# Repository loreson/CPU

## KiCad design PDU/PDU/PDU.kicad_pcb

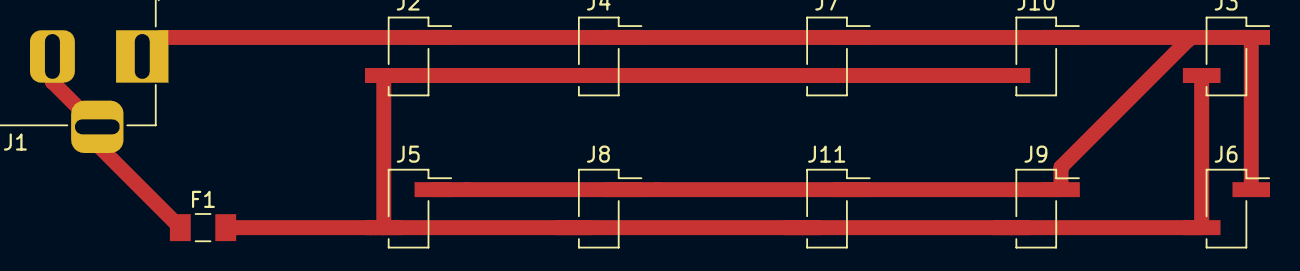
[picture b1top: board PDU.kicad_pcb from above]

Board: 2 copper layers, 12 parts (0 on the bottom side), 3 nets.

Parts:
F1: Fuse_Small; Fuse_1206_3216Metric_Pad1.39x1.80mm_HandSolder
J1: Barrel_Jack; BarrelJack_Horizontal
J2, J3, J4, J5, J6, J7, J8, J9, J10, J11: Conn_01x02_Male; PinHeader_1x02_P2.54mm_Vertical_SMD_Pin1Right

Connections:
unnamed: F1.1, J1.2, J1.3
unnamed: F1.2, J2.2, J3.2, J4.2, J5.2, J6.2, J7.2, J8.2, J9.2, J10.2, J11.2
unnamed: J1.1, J2.1, J3.1, J4.1, J5.1, J6.1, J7.1, J8.1, J9.1, J10.1, J11.1

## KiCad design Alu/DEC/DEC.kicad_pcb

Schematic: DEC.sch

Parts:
C1, C2: 100nF; C_0805_2012Metric_Pad1.29x1.40mm_HandSolder
J1: Conn_01x08; PinHeader_1x08_P2.54mm_Vertical
J2: Conn_01x09; PinHeader_1x09_P2.54mm_Vertical
J3: Conn_01x02; PinHeader_1x02_P2.54mm_Vertical
R10, R11, R12: 0; R_1206_3216Metric_Pad1.39x1.80mm_HandSolder
U1, U2: 74LS283; SOIC-16_3.9x9.9mm_P1.27mm

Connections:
/C_OUT: J2.1, U2.9; also elsewhere on the board
/X0: J1.8, U1.5
/X1: J1.7, U1.3
/X2: J1.6, U1.14
/X3: J1.5, U1.12
/X4: J1.4, U2.5
/X5: J1.3, U2.3
/X6: J1.2, U2.14
/X7: J1.1, U2.12
/Z0: J2.9, U1.4; also elsewhere on the board
/Z1: J2.8, U1.1; also elsewhere on the board
/Z2: J2.7, U1.13; also elsewhere on the board
/Z3: J2.6, R11.1; also elsewhere on the board
/Z4: J2.5, U2.4; also elsewhere on the board
/Z5: J2.4, U2.1; also elsewhere on the board
/Z6: J2.3, U2.13; also elsewhere on the board
/Z7: J2.2, R10.1; also elsewhere on the board
GND: C1.2, C2.2, J3.2, R12.1, R12.2, U1.7, U1.8, U2.8; also elsewhere on the board
unnamed: R10.2, U2.10
unnamed: R11.2, U1.10
unnamed: U1.9, U2.7
VCC: C1.1, C2.1, J3.1, U1.2, U1.6, U1.11, U1.15, U1.16, U2.2, U2.6, U2.11, U2.15, U2.16; also elsewhere on the board

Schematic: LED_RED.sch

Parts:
D1: RED; LED_0805_2012Metric_Pad1.12x1.40mm_HandSolder
Q1: 2N7002; SOT-23
R1: 1k; R_0805_2012Metric

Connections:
/Z0: Q1.1 (G); also elsewhere on the board
GND: Q1.2 (S); also elsewhere on the board
unnamed: D1.1, R1.1
unnamed: Q1.3 (D), R1.2
VCC: D1.2; also elsewhere on the board

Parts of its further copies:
D2, D3, D4, D5, D6, D7, D9: RED; LED_0805_2012Metric_Pad1.12x1.40mm_HandSolder
Q2, Q3, Q4, Q5, Q6, Q7, Q9: 2N7002; SOT-23
R2, R3, R4, R5, R6, R7, R9: 1k; R_0805_2012Metric

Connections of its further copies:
/Z1: Q2.1 (G); also elsewhere on the board
/Z2: Q3.1 (G); also elsewhere on the board
/Z3: Q4.1 (G); also elsewhere on the board
/Z4: Q5.1 (G); also elsewhere on the board
/Z5: Q6.1 (G); also elsewhere on the board
/Z6: Q7.1 (G); also elsewhere on the board
/Z7: Q9.1 (G); also elsewhere on the board
GND: Q2.2 (S), Q3.2 (S), Q4.2 (S), Q5.2 (S), Q6.2 (S), Q7.2 (S), Q9.2 (S); also elsewhere on the board
unnamed: D2.1, R2.1
unnamed: D3.1, R3.1
unnamed: D4.1, R4.1
unnamed: D5.1, R5.1
unnamed: D6.1, R6.1
unnamed: D7.1, R7.1
unnamed: D9.1, R9.1
unnamed: Q2.3 (D), R2.2
unnamed: Q3.3 (D), R3.2
unnamed: Q4.3 (D), R4.2
unnamed: Q5.3 (D), R5.2
unnamed: Q6.3 (D), R6.2
unnamed: Q7.3 (D), R7.2
unnamed: Q9.3 (D), R9.2
VCC: D2.2, D3.2, D4.2, D5.2, D6.2, D7.2, D9.2; also elsewhere on the board

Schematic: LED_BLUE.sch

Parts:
D8: BLUE; LED_0805_2012Metric_Pad1.12x1.40mm_HandSolder
Q8: 2N7002; SOT-23
R8: 820R; R_0805_2012Metric_Pad1.29x1.40mm_HandSolder

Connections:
/C_OUT: Q8.1 (G); also elsewhere on the board
GND: Q8.2 (S); also elsewhere on the board
unnamed: D8.1, R8.1
unnamed: Q8.3 (D), R8.2
VCC: D8.2; also elsewhere on the board

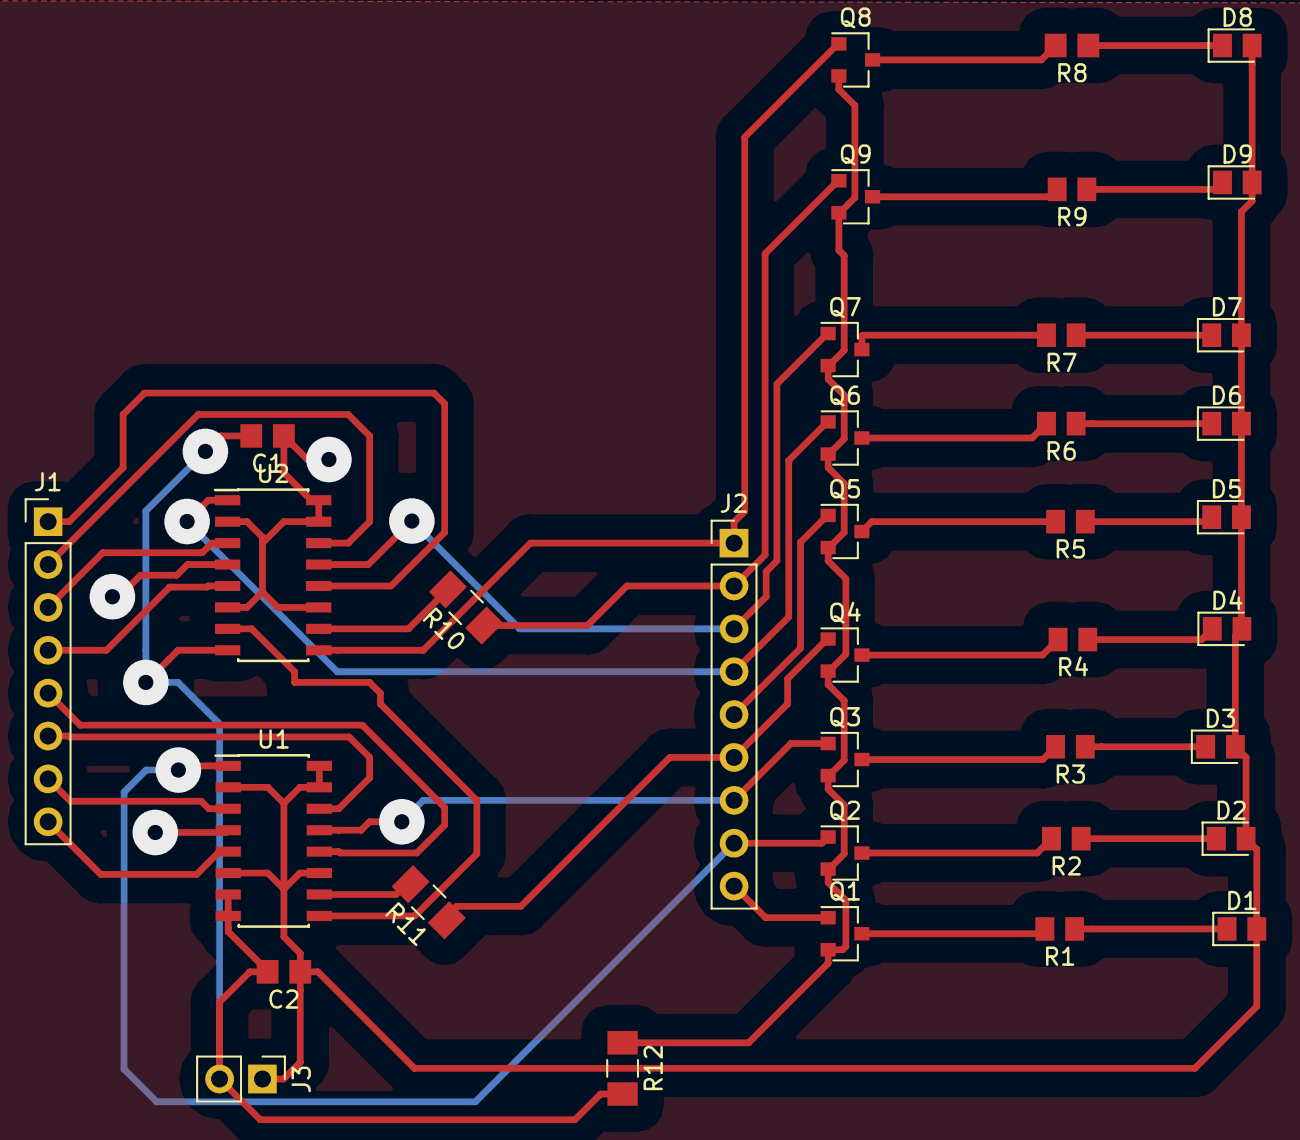
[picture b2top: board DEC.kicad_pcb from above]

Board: 4 copper layers, 37 parts (0 on the bottom side), 40 nets.

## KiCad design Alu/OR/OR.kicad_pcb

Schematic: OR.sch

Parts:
C1, C2: 100nF; C_0805_2012Metric
J1, J2, J4: Conn_01x08; PinHeader_1x08_P2.54mm_Vertical
J3: Conn_01x02_Male; PinHeader_1x02_P2.54mm_Vertical
R1, R2, R3: 0; R_1206_3216Metric_Pad1.39x1.80mm_HandSolder
U1, U2: 74LS32; SOIC-14_3.9x8.7mm_P1.27mm

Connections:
/X0: J1.8, U1.1
/X1: J1.7, U1.4
/X2: J1.6, U1.9
/X3: J1.5, U1.12
/X4: J1.4, U2.1
/X5: J1.3, U2.4
/X6: J1.2, U2.9
/X7: R2.1, U2.12
/Y0: J2.8, U1.2
/Y1: J2.7, U1.5
/Y2: J2.6, U1.10
/Y3: J2.5, U1.13
/Y4: R1.1, U2.2
/Y5: J2.3, U2.5
/Y6: J2.2, U2.10
/Y7: J2.1, U2.13
/Z0: J4.8, U1.3; also elsewhere on the board
/Z1: J4.7, U1.6; also elsewhere on the board
/Z2: J4.6, U1.8; also elsewhere on the board
/Z3: J4.5, U1.11; also elsewhere on the board
/Z4: J4.4, U2.3; also elsewhere on the board
/Z5: J4.3, U2.6; also elsewhere on the board
/Z6: J4.2, R3.1, U2.8
/Z7: J4.1, U2.11; also elsewhere on the board
/sheet5C411B65/X: R3.2; also elsewhere on the board
GND: C1.2, C2.2, J3.2, U1.7, U2.7; also elsewhere on the board
unnamed: J1.1, R2.2
unnamed: J2.4, R1.2
VCC: C1.1, C2.1, J3.1, U1.14, U2.14; also elsewhere on the board

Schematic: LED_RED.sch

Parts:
D1: RED; LED_0805_2012Metric_Pad1.12x1.40mm_HandSolder
Q1: 2N7002; SOT-23
R4: 1k; R_0805_2012Metric

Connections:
/Z0: Q1.1 (G); also elsewhere on the board
GND: Q1.2 (S); also elsewhere on the board
unnamed: D1.1, R4.1
unnamed: Q1.3 (D), R4.2
VCC: D1.2; also elsewhere on the board

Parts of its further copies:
D2, D3, D4, D5, D6, D7, D8: RED; LED_0805_2012Metric_Pad1.12x1.40mm_HandSolder
Q2, Q3, Q4, Q5, Q6, Q7, Q8: 2N7002; SOT-23
R5, R6, R7, R8, R9, R10, R11: 1k; R_0805_2012Metric

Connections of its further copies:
/Z1: Q2.1 (G); also elsewhere on the board
/Z2: Q3.1 (G); also elsewhere on the board
/Z3: Q4.1 (G); also elsewhere on the board
/Z4: Q5.1 (G); also elsewhere on the board
/Z5: Q6.1 (G); also elsewhere on the board
/Z7: Q8.1 (G); also elsewhere on the board
/sheet5C411B65/X: Q7.1 (G); also elsewhere on the board
GND: Q2.2 (S), Q3.2 (S), Q4.2 (S), Q5.2 (S), Q6.2 (S), Q7.2 (S), Q8.2 (S); also elsewhere on the board
unnamed: D2.1, R5.1
unnamed: D3.1, R6.1
unnamed: D4.1, R7.1
unnamed: D5.1, R8.1
unnamed: D6.1, R9.1
unnamed: D7.1, R10.1
unnamed: D8.1, R11.1
unnamed: Q2.3 (D), R5.2
unnamed: Q3.3 (D), R6.2
unnamed: Q4.3 (D), R7.2
unnamed: Q5.3 (D), R8.2
unnamed: Q6.3 (D), R9.2
unnamed: Q7.3 (D), R10.2
unnamed: Q8.3 (D), R11.2
VCC: D2.2, D3.2, D4.2, D5.2, D6.2, D7.2, D8.2; also elsewhere on the board

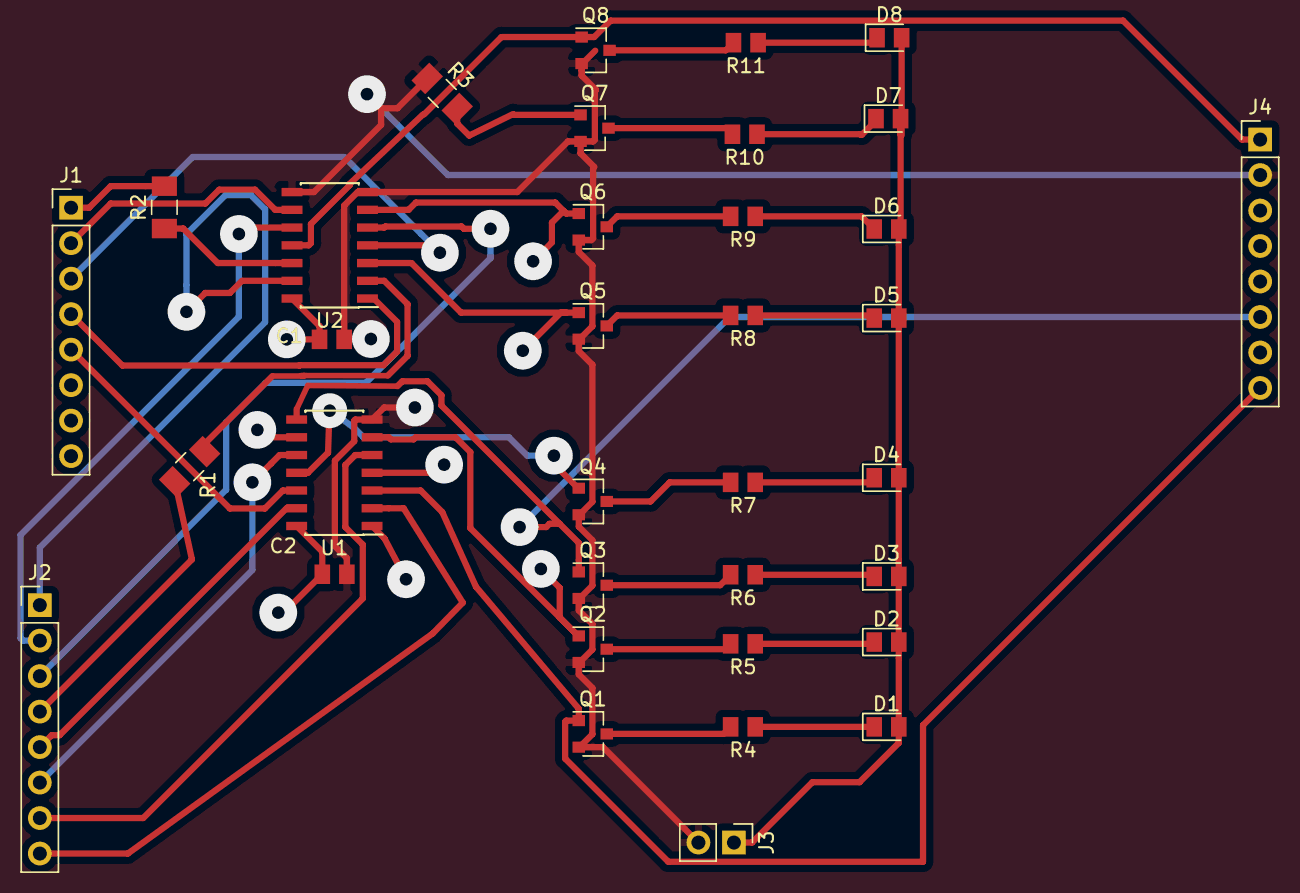
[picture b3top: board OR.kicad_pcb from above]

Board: 6 copper layers, 35 parts (0 on the bottom side), 45 nets.

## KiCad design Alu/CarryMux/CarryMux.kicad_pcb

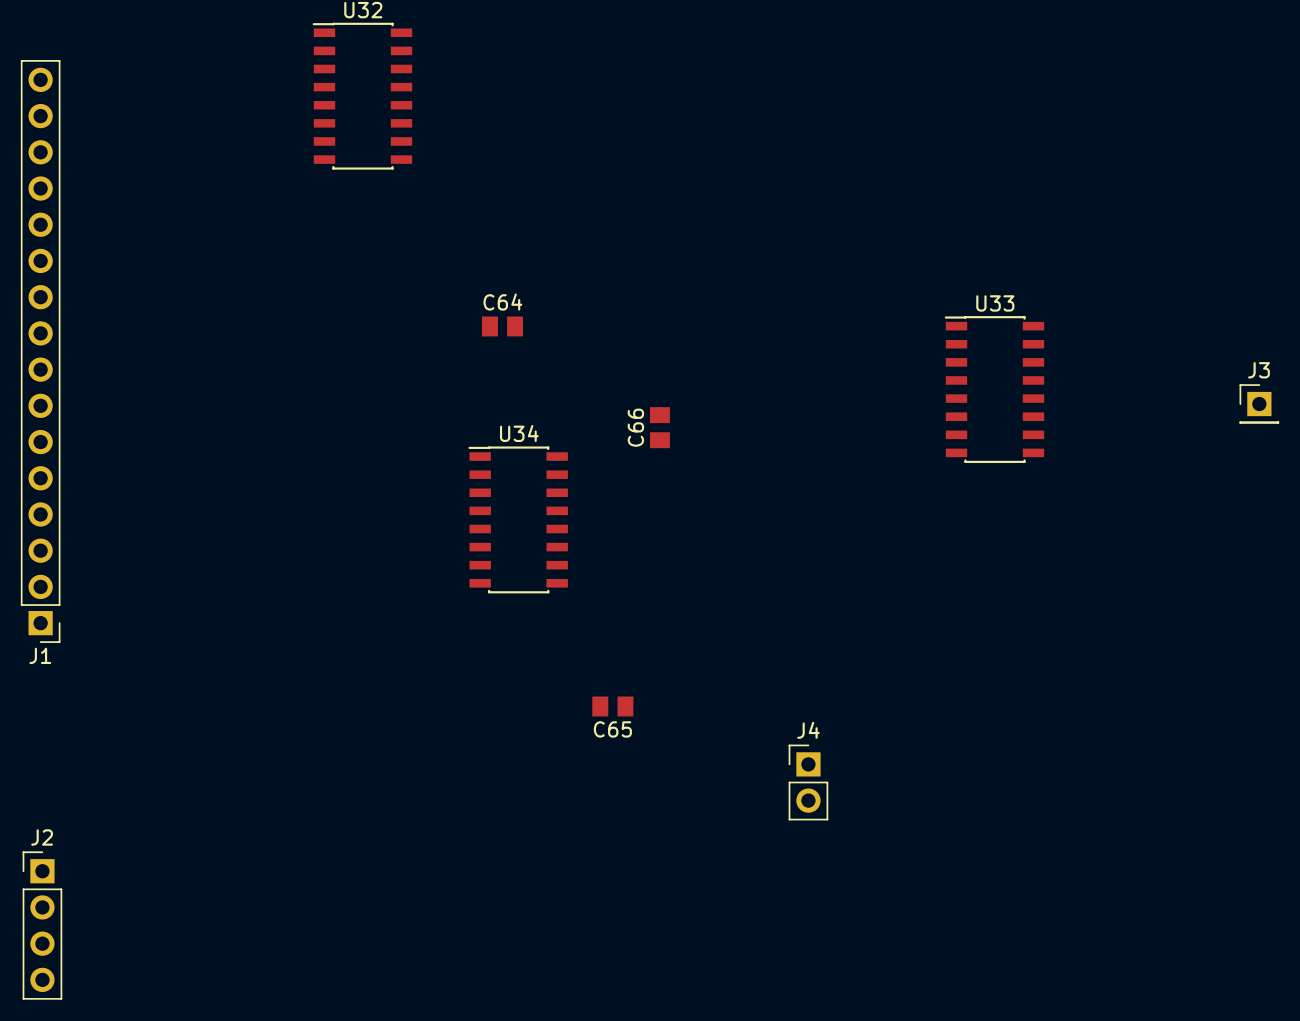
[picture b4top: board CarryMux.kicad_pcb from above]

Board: 2 copper layers, 10 parts (0 on the bottom side), 25 nets, no tracks yet.

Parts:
C64, C65, C66: 100nF; C_0805_2012Metric
J1: Conn_01x16; PinHeader_1x16_P2.54mm_Vertical
J2: Conn_01x04; PinHeader_1x04_P2.54mm_Vertical
J3: Conn_01x01; PinHeader_1x01_P2.54mm_Vertical
J4: Conn_01x02; PinHeader_1x02_P2.54mm_Vertical
U32, U34: 74LS151; SOIC-16_3.9x9.9mm_P1.27mm
U33: 74LS157; SOIC-16_3.9x9.9mm_P1.27mm

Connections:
/S0: J2.4, U33.1
/S1: J2.3, U32.11, U34.11
/S2: J2.2, U32.10, U34.10
/S3: J2.1, U32.9, U34.9
/X0: J1.16, U32.4
/X1: J1.15, U32.3
/X2: J1.14, U32.2
/X3: J1.13, U32.1
/X4: J1.12, U32.15
/X5: J1.11, U32.14
/X6: J1.10, U32.13
/X7: J1.9, U32.12
/X8: J1.8, U34.4
/X9: J1.7, U34.3
/X10: J1.6, U34.2
/X11: J1.5, U34.1
/X12: J1.4, U34.15
/X13: J1.3, U34.14
/X14: J1.2, U34.13
/X15: J1.1, U34.12
GND: C64.2, C65.2, C66.2, J4.2, U32.7, U32.8, U33.5, U33.6, U33.8, U33.10, U33.11, U33.13, U33.14, U33.15, U34.7, U34.8
unnamed: J3.1, U33.4
unnamed: U32.5, U33.2
unnamed: U33.3, U34.5
VCC: C64.1, C65.1, C66.1, J4.1, U32.16, U33.16, U34.16
